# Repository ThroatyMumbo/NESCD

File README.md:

# NESCD-001

An unofficial homemade CD add-on for the NES, just because!

This repo contains the schematics, PCB, 3D printable STLs for the shell, sticker labels, and the firmware.

## How it works

It's basically an RP2350B hooked up to both an Everdrive N8 Pro and an IDE CD drive. It reads the game ROM off the CD, uploads it to the Everdrive over USB
and asks the menu to install it, then watches a mailbox byte in the cart's CHR RAM for the game to ask for music. The RP2350B is the coordinator in the
middle that bridges the NES/Everdrive and the CD drive.

Project video: https://www.youtube.com/watch?v=6D8RWVwW4ZI

## Hardware
- The main PCB (see [pcb/](pcb/))
- A standard 40-pin IDE CD drive
- Everdrive N8 Pro

## Build

```
cd firmware && ./flash.sh
```

## Making a disc

The demo game needs [cc65](https://cc65.github.io/) (`ca65`/`ld65`), plus
`python3` with `numpy`, `ffmpeg` for the audio, and `xorriso` to burn.

```
cd game && make         # demo.nes, four music tracks, and build/demo.img
cd game && make burn    # burn build/demo.img and read it back to check
```

To put your own game on a disc, pass [`mkgamedisc.py`](firmware/tools/mkgamedisc.py)
an iNES ROM and one track per music byte:

```
python3 firmware/tools/mktrack.py theme.wav -o theme.rom --loop-start 4.2
python3 firmware/tools/mkgamedisc.py -o mygame.img --title "MY GAME" --nes mygame.nes --track 1=theme.rom --verify
firmware/burn.sh mygame.img
```

## Using it

If everything goes right, you should be able to just put a burned disc into the CD drive while the NES is on and sitting on the Everdrive menu.
It'll auto-boot the game once it's read and uploaded to the Everdrive.

### Playing an audio CD

Arguably the most practical use for this thing: A CD player!

Insert the CD while on the Everdrive menu and it should automatically launch the player.

## FAQ

### What?
Great question! I came up with the idea for this project while reading about the canceled SNES CD-ROM add-on. I was originally going to make my own
version of that add-on, but decided it'd be funnier and weirder if I took it a step further and made one for NES.

### Why?
Because it's fun.

### Who?
It's me! Your old pal - Throaty Mumbo!

### Where are the FMVs you showed in the video?
I chose not to include any FMV-related code here because to get that working I had to semi-reverse engineer
Something Nerdy's [Bad Apple!! Ultimate NES Demake](https://somethingnerdy.com/downloads/), which is currently closed source.
The team has mentioned they're planning to formally open source their MXM mapper (which this demo presumably uses, actually not sure)
once their game *Former Dawn* is released. I didn't feel good about publishing reverse engineered code from an indie development team
for my stupid meme project, especially when they have plans to release it themselves.

### Why not stream audio from the Everdrive?
I originally wanted to do this, but was hitting a ceiling on the Everdrive USB bandwidth. I'd likely have to add some form of aggressive compression
to make room. It's also a nice touch to use the expansion port instead.

The USB cable poking out on the front is by far the biggest blemish on the design of this contraption, so I did look at moving everything to the
expansion port. Unfortunately the bandwidth there is even more limited than the USB route.

Plus, the expansion port audio allows more flexibility with mixing and volume control - hence the volume knob on the front.

### How is this thing powered?
A single molex cable from a wall adapter ([this one](https://www.amazon.com/Coolerguys-100-240v-Molex-Power-Adapter/dp/B000MGG6SC) in particular).
The 5V/12V rails are split between the CD drive and the board + the NES output. I took the end of a spare NES power cable and hooked it up to
a buck converter that converts the 12V input to ~9.5V so you can power the NES as well (the plug pokes out of the top of the box). That way
you only need one wall outlet to get the entire thing running. You can also power the NES separately from its regular adapter - the plug
coming out of the NESCD is optional.

### Couldn't you power everything off VRAW?
This was my initial plan, but it seemed tight considering the stock NES adapter (1.3A) has to power the NES, Everdrive, RP2350, DAC, and the CD drive.
The power adapter for that Fideco drive sled I tested with initially outputs at 2A, so I figured a dedicated 2A molex adapter (which supposedly outputs 2A on
5V and 12V each, at least according to the label) would be the minimum. But honestly I didn't actually test running the CD drive and everything else off
VRAW at the same time, so this was more of a cautious choice than based off of objective measurement. If it works it'd be a nice improvement for
an eventual v2 design.

### How do you get back to the Everdrive menu once you've inserted a disc?
This is still something I'm trying to figure out. AFAIK there's no way to trigger a soft reset on the NES. However one guaranteed solution is to
hook up the NES power output rail to a relay switch. That way if the board ever needs the NES to reset, it can just turn it on and off from the
source. Not super elegant but it should work.

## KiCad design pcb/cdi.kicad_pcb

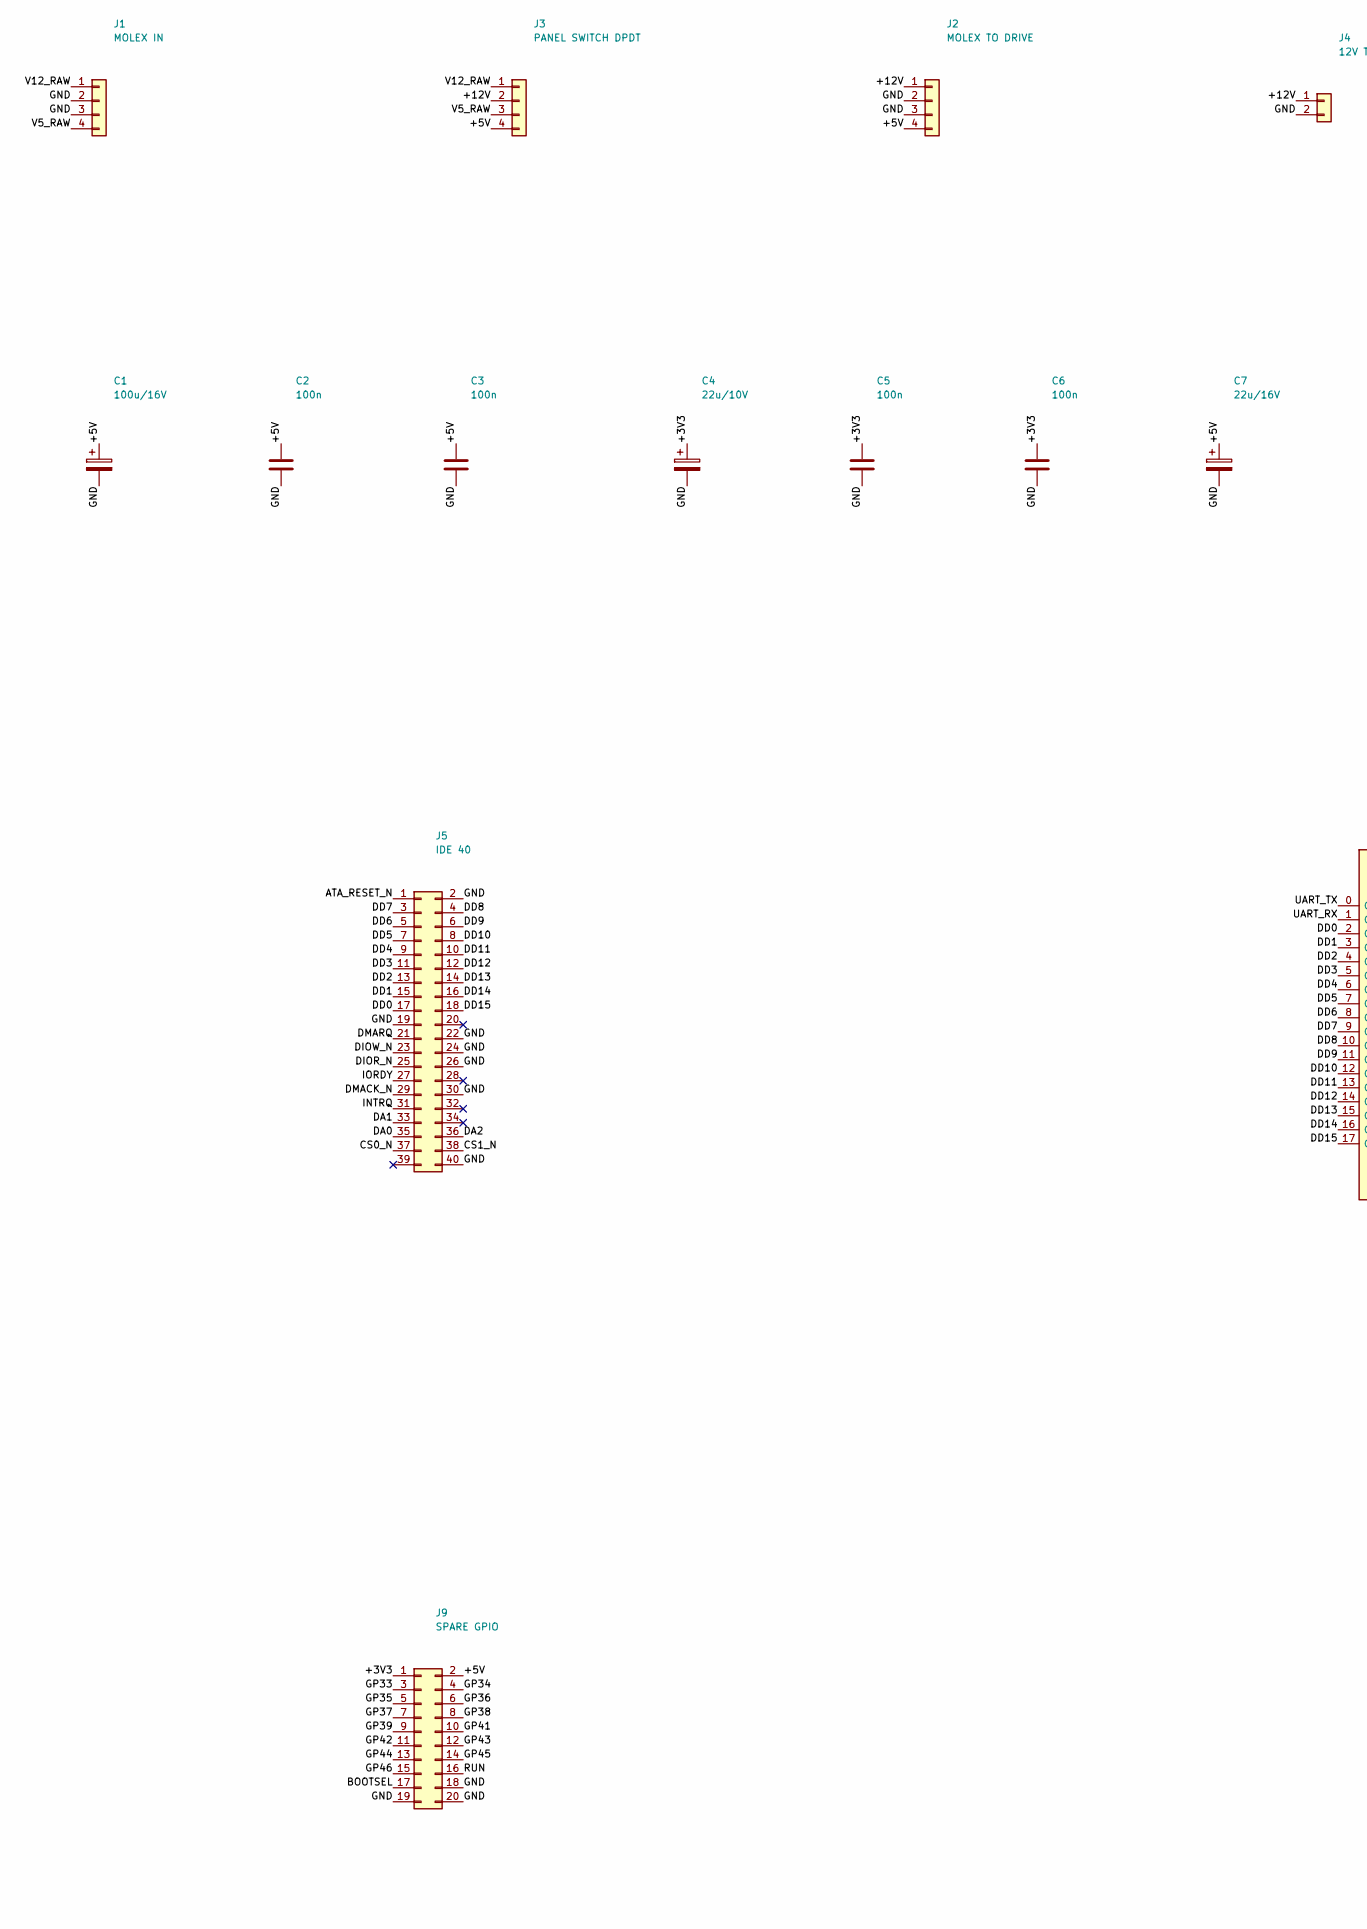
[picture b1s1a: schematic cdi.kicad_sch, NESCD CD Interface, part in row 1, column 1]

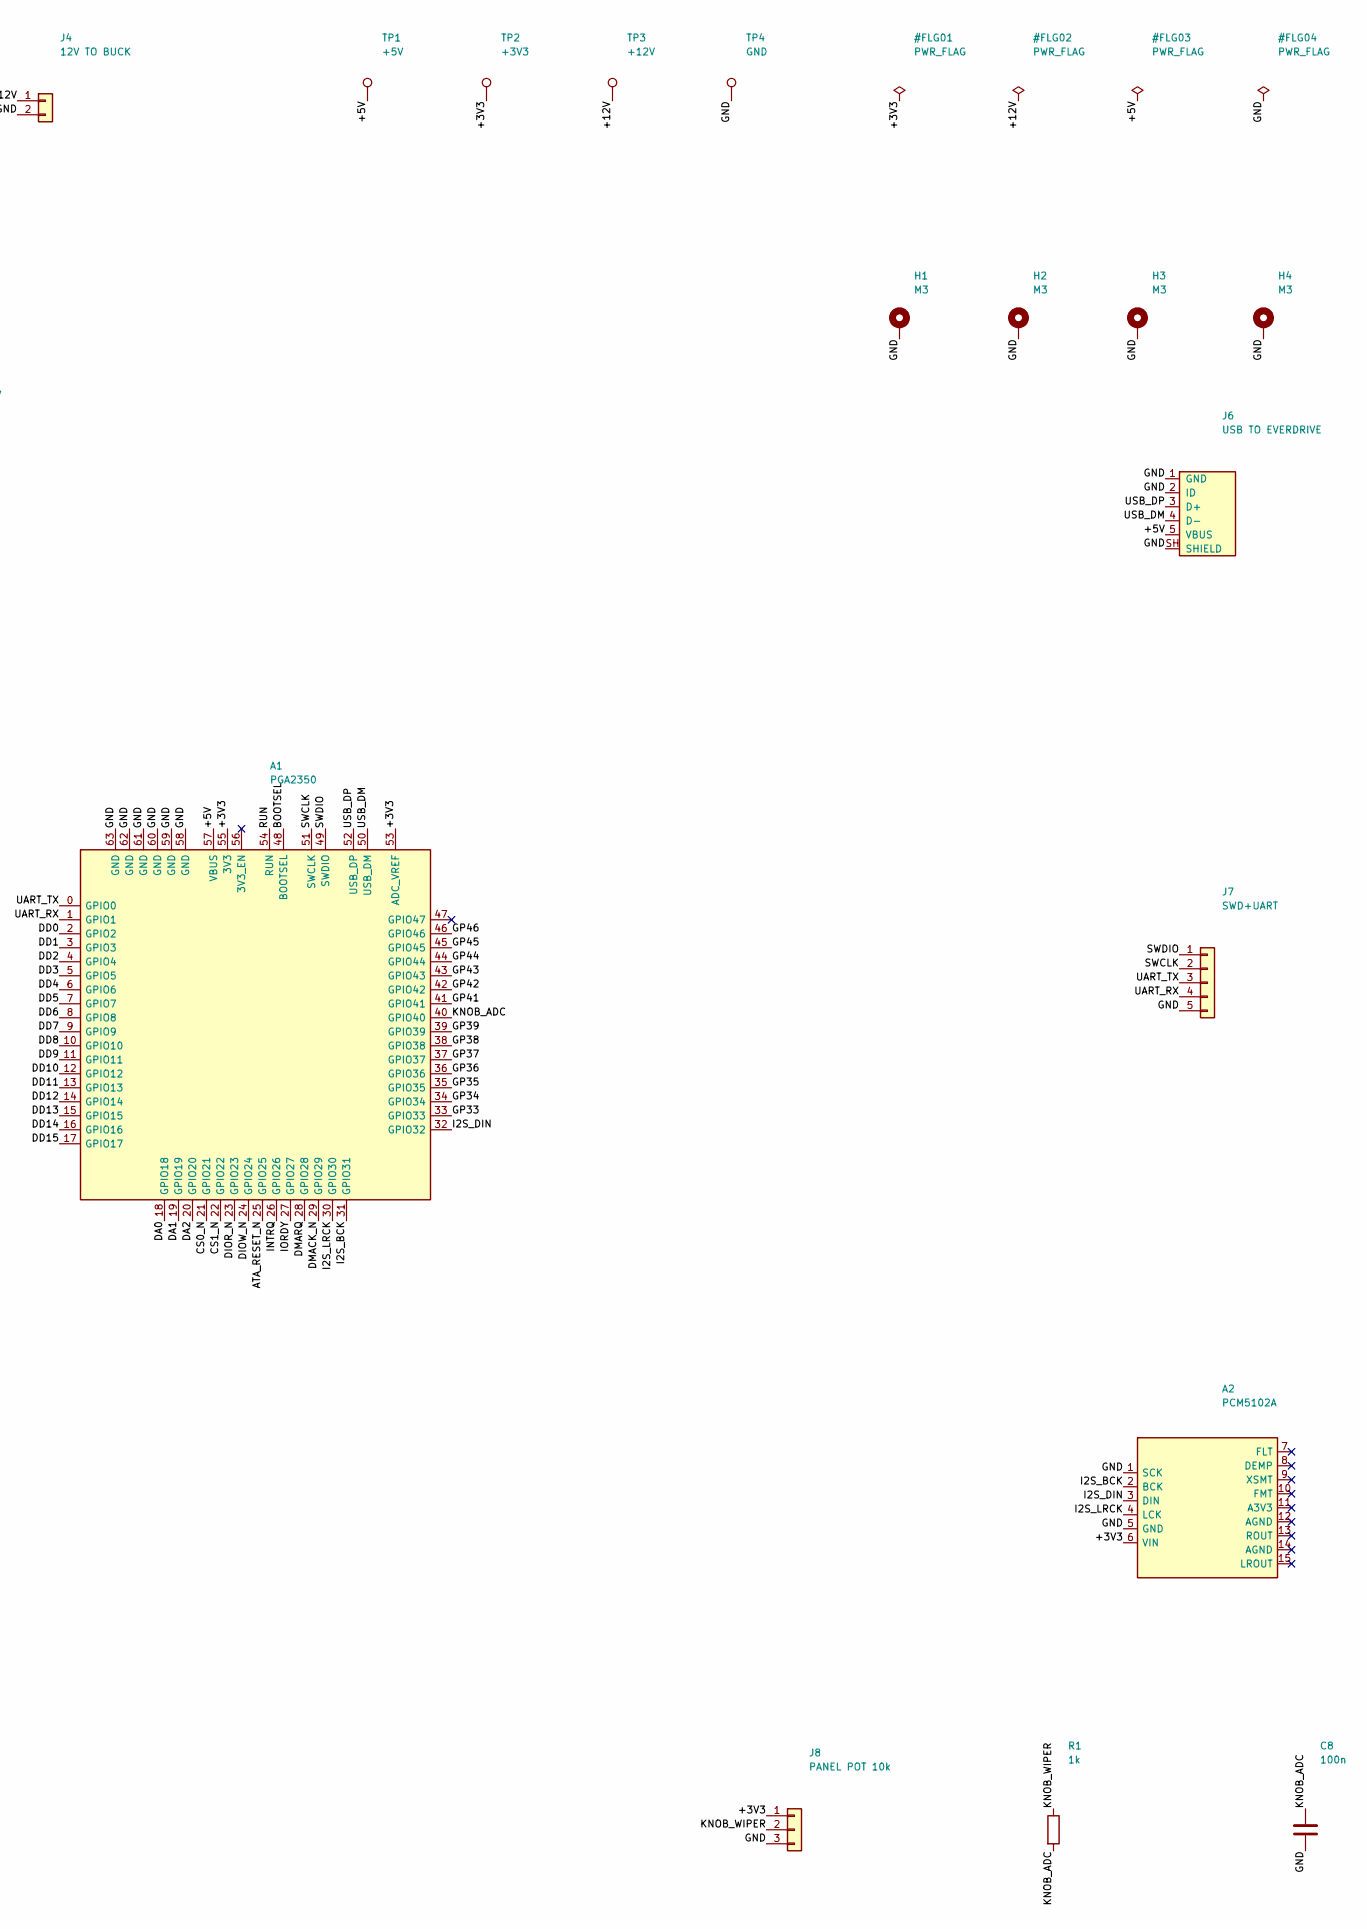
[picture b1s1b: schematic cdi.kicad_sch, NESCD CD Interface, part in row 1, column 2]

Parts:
A1: PGA2350; Pimoroni_PGA2350
A2: PCM5102A; PCM5102A_Board
C1: 100u/16V; CP_Radial_D6.3mm_P2.50mm
C2, C3, C5, C6, C8: 100n; C_Disc_D5.0mm_W2.5mm_P5.00mm
C4: 22u/10V; CP_Radial_D5.0mm_P2.50mm
C7: 22u/16V; CP_Radial_D5.0mm_P2.50mm
H1, H2, H3, H4: M3; MountingHole_3.2mm_M3_DIN965_Pad
J1: MOLEX IN; TE_MATE-N-LOK_350211-1_1x04_P5.08mm_Vertical
J2: MOLEX TO DRIVE; TE_MATE-N-LOK_350211-1_1x04_P5.08mm_Vertical
J3: PANEL SWITCH DPDT; TerminalBlock_Phoenix_MKDS-1,5-4-5.08_1x04_P5.08mm_Horizont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
J4: 12V TO BUCK; TerminalBlock_Phoenix_MKDS-1,5-2-5.08_1x02_P5.08mm_Horizont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
J5: IDE 40; IDC-Header_2x20_P2.54mm_Vertical
J6: USB TO EVERDRIVE; USB_Micro_DIP_1x05_P2.54mm
J7: SWD+UART; PinHeader_1x05_P2.54mm_Vertical
J8: PANEL POT 10k; PinHeader_1x03_P2.54mm_Vertical
J9: SPARE GPIO; PinHeader_2x10_P2.54mm_Vertical
R1: 1k; R_Axial_DIN0207_L6.3mm_D2.5mm_P7.62mm_Horizontal
TP1: +5V; TestPoint_THTPad_D1.5mm_Drill0.7mm
TP2: +3V3; TestPoint_THTPad_D1.5mm_Drill0.7mm
TP3: +12V; TestPoint_THTPad_D1.5mm_Drill0.7mm
TP4: GND; TestPoint_THTPad_D1.5mm_Drill0.7mm

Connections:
/+3V3: A1.53 (ADC_VREF), A1.55 (3V3), A2.6 (VIN), C4.1, C5.1, C6.1, J8.1, J9.1, TP2.1 (1_1)
/+5V: A1.57 (VBUS), C1.1, C2.1, C3.1, C7.1, J2.4, J3.4, J6.5 (VBUS), J9.2, TP1.1 (1_1)
/+12V: J2.1, J3.2, J4.1, TP3.1 (1_1)
/ATA_RESET_N: A1.25 (GPIO25), J5.1
/BOOTSEL: A1.48 (BOOTSEL), J9.17
/CS0_N: A1.21 (GPIO21), J5.37
/CS1_N: A1.22 (GPIO22), J5.38
/DA0: A1.18 (GPIO18), J5.35
/DA1: A1.19 (GPIO19), J5.33
/DA2: A1.20 (GPIO20), J5.36
/DD0: A1.2 (GPIO2), J5.17
/DD1: A1.3 (GPIO3), J5.15
/DD2: A1.4 (GPIO4), J5.13
/DD3: A1.5 (GPIO5), J5.11
/DD4: A1.6 (GPIO6), J5.9
/DD5: A1.7 (GPIO7), J5.7
/DD6: A1.8 (GPIO8), J5.5
/DD7: A1.9 (GPIO9), J5.3
/DD8: A1.10 (GPIO10), J5.4
/DD9: A1.11 (GPIO11), J5.6
/DD10: A1.12 (GPIO12), J5.8
/DD11: A1.13 (GPIO13), J5.10
/DD12: A1.14 (GPIO14), J5.12
/DD13: A1.15 (GPIO15), J5.14
/DD14: A1.16 (GPIO16), J5.16
/DD15: A1.17 (GPIO17), J5.18
/DIOR_N: A1.23 (GPIO23), J5.25
/DIOW_N: A1.24 (GPIO24), J5.23
/DMACK_N: A1.29 (GPIO29), J5.29
/DMARQ: A1.28 (GPIO28), J5.21
/GND: A1.58 (GND), A1.59 (GND), A1.60 (GND), A1.61 (GND), A1.62 (GND), A1.63 (GND), A2.1 (SCK), A2.5 (GND), C1.2, C2.2, C3.2, C4.2, C5.2, C6.2, C7.2, C8.2, H1.1 (1_1), H2.1 (1_1), H3.1 (1_1), H4.1 (1_1), J1.2, J1.3, J2.2, J2.3, J4.2, J5.2, J5.19, J5.22, J5.24, J5.26, J5.30, J5.40, J6.1 (GND), J6.2 (ID), J6.SH (SHIELD), J7.5, J8.3, J9.18, J9.19, J9.20, TP4.1 (1_1)
/GP33: A1.33 (GPIO33), J9.3
/GP34: A1.34 (GPIO34), J9.4
/GP35: A1.35 (GPIO35), J9.5
/GP36: A1.36 (GPIO36), J9.6
/GP37: A1.37 (GPIO37), J9.7
/GP38: A1.38 (GPIO38), J9.8
/GP39: A1.39 (GPIO39), J9.9
/GP41: A1.41 (GPIO41), J9.10
/GP42: A1.42 (GPIO42), J9.11
/GP43: A1.43 (GPIO43), J9.12
/GP44: A1.44 (GPIO44), J9.13
/GP45: A1.45 (GPIO45), J9.14
/GP46: A1.46 (GPIO46), J9.15
/I2S_BCK: A1.31 (GPIO31), A2.2 (BCK)
/I2S_DIN: A1.32 (GPIO32), A2.3 (DIN)
/I2S_LRCK: A1.30 (GPIO30), A2.4 (LCK)
/INTRQ: A1.26 (GPIO26), J5.31
/IORDY: A1.27 (GPIO27), J5.27
/KNOB_ADC: A1.40 (GPIO40), C8.1, R1.2
/KNOB_WIPER: J8.2, R1.1
/RUN: A1.54 (RUN), J9.16
/SWCLK: A1.51 (SWCLK), J7.2
/SWDIO: A1.49 (SWDIO), J7.1
/UART_RX: A1.1 (GPIO1), J7.4
/UART_TX: A1.0 (GPIO0), J7.3
/USB_DM: A1.50 (USB_DM), J6.4 (D-)
/USB_DP: A1.52 (USB_DP), J6.3 (D+)
/V5_RAW: J1.4, J3.3
/V12_RAW: J1.1, J3.1

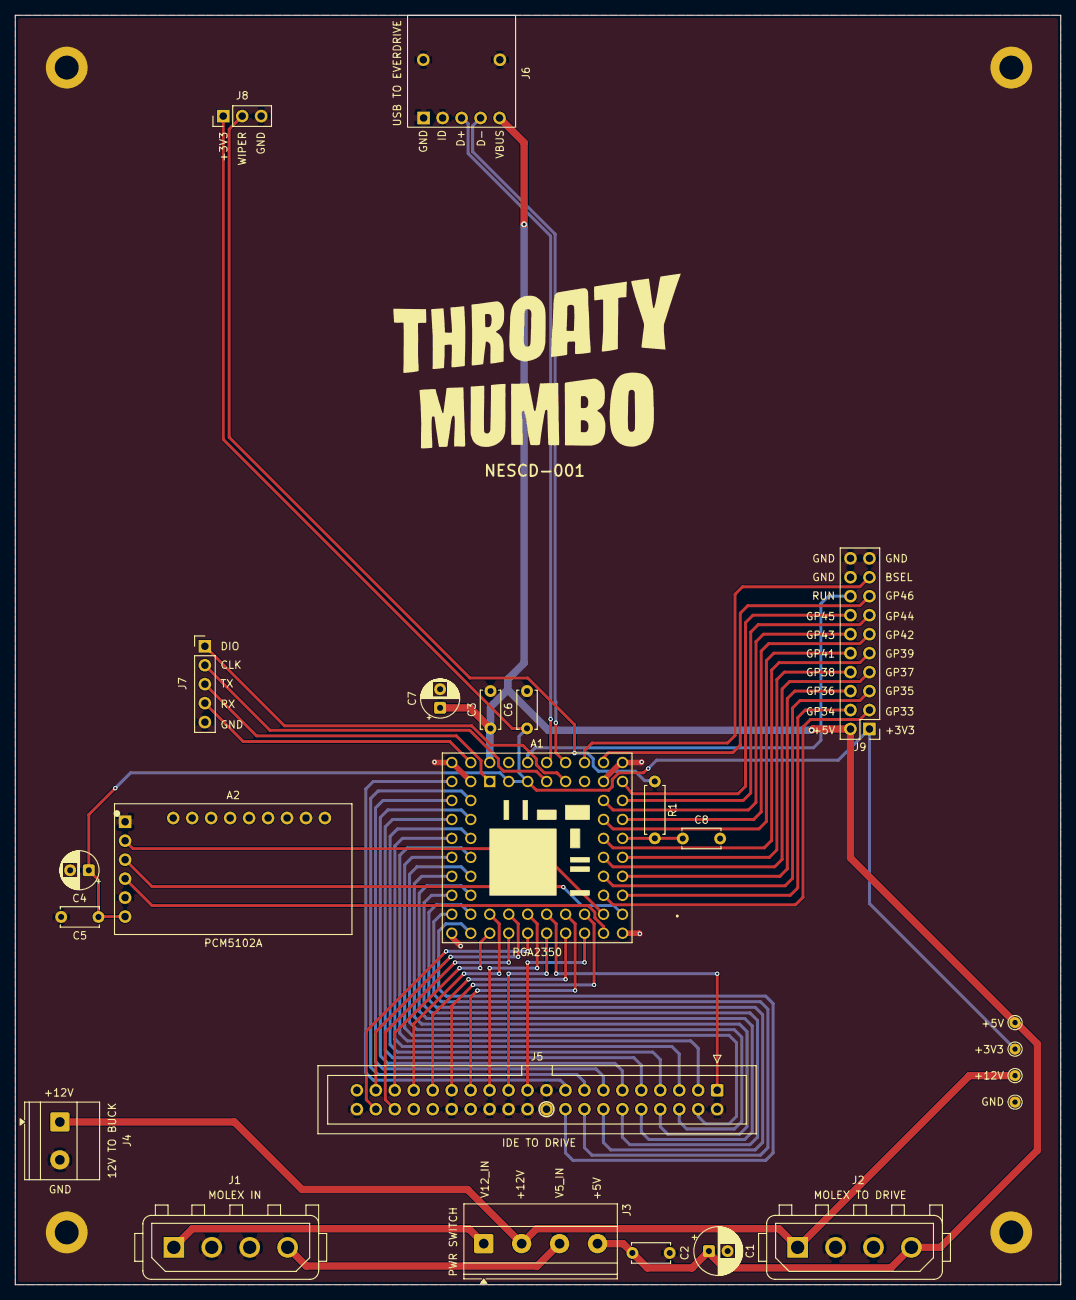
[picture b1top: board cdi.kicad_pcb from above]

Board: 2 copper layers, 140.0 x 170.0 mm, 28 parts (0 on the bottom side), 60 nets.

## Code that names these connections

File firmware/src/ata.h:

// ata.h - Parallel ATA taskfile host for the RP2350B (PGA2350).
//
// Role: HOST. This MCU is the IDE controller and drives any ATAPI CD-ROM
// (developed against a Pacific Digital MACH 52). The PACKET layer is atapi.c.
//
// The RP2350 is 5V tolerant, so the 40-pin ATA bus (5V TTL) connects DIRECTLY
// to GPIO - no level shifters, no transceivers.
//
// 40-pin ATA cable. Pin 20 is the key (no contact); tie every ground:
//   GND     pins 2,19,22,24,26,30,40
//   unused  pin 28 CSEL, 32 IOCS16#, 34 PDIAG#, 39 DASP#
//
// Jumper the drive to MASTER: it is the only device on the bus.

#ifndef ATA_H
#define ATA_H

#include <stdint.h>
#include <stdbool.h>
#include <stddef.h>
#include "pico/stdlib.h"

// ---- GPIO assignment (RP2350B / PGA2350) --------------------------------
// Reserved on this board: GP0/GP1 = UART0 console (debugprobe), GP47 = PSRAM CS.
// The bus is one contiguous block, GP2..GP29: inside a PIO GPIOBASE=0 window and
// below GP31, so gpio_get_all() and gpio_put_masked() still move the whole bus
// in one instruction.
#define PIN_DD0    2u          // DD0..DD15 = GPIO2..GPIO17 (bidirectional)
#define DD_MASK    (0xFFFFu << PIN_DD0)
#define PIN_DA0    18u         // out: register select bit 0   (ATA pin 35)
#define PIN_DA1    19u         // out: register select bit 1   (ATA pin 33)
#define PIN_DA2    20u         // out: register select bit 2   (ATA pin 36)
#define PIN_CS0    21u         // out: /CS0 command block      (ATA pin 37)
#define PIN_CS1    22u         // out: /CS1 control block      (ATA pin 38)
#define PIN_DIOR   23u         // out: /DIOR read strobe       (ATA pin 25)
#define PIN_DIOW   24u         // out: /DIOW write strobe      (ATA pin 23)
#define PIN_RESET  25u         // out: /RESET                  (ATA pin 1)
#define PIN_INTRQ  26u         // in : INTRQ                   (ATA pin 31)
#define PIN_IORDY  27u         // in : IORDY                   (ATA pin 27)
#define PIN_DMARQ  28u         // in : DMARQ                   (ATA pin 21)
#define PIN_DMACK  29u         // out: /DMACK                  (ATA pin 29)

// DA0..2 + both chip selects move together in one masked store.
#define ATA_ADDR_MASK (0x1Fu << PIN_DA0)

// DD0..DD15 interleave across the connector's two rows. Verify each line while
// wiring: ATA 17,15,13,11,9,7,5,3 = DD0..DD7, ATA 4,6,8,10,12,14,16,18 = DD8..DD15.

// ---- register blocks ----------------------------------------------------
#define ATA_CS_CMD 0u          // assert /CS0: command block
#define ATA_CS_CTL 1u          // assert /CS1: control block

// Command block (ATA_CS_CMD), selected by DA2:0.
#define ATA_REG_DATA      0u   // 16-bit
#define ATA_REG_ERROR     1u   // read
#define ATA_REG_FEATURES  1u   // write
#define ATA_REG_INTREASON 2u   // read  (ATAPI)
#define ATA_REG_SECCOUNT  2u   // write
#define ATA_REG_LBA_LOW   3u
#define ATA_REG_BCOUNT_LO 4u   // byte count low  (ATAPI)
#define ATA_REG_BCOUNT_HI 5u   // byte count high (ATAPI)
#define ATA_REG_DEVICE    6u   // DEV = bit 4
#define ATA_REG_STATUS    7u   // read
#define ATA_REG_COMMAND   7u   // write

// Control block (ATA_CS_CTL), DA=6.
#define ATA_REG_ALTSTATUS 6u   // read  (does not clear INTRQ)
#define ATA_REG_DEVCTL    6u   // write

// ---- status / device control bits ---------------------------------------
#define ATA_ST_BSY   0x80u
#define ATA_ST_DRDY  0x40u
#define ATA_ST_DF    0x20u
#define ATA_ST_DSC   0x10u
#define ATA_ST_DRQ   0x08u
#define ATA_ST_ERR   0x01u

#define ATA_DEVCTL_SRST 0x04u
#define ATA_DEVCTL_NIEN 0x02u

// ---- commands -----------------------------------------------------------
#define ATA_CMD_DEVICE_RESET    0x08u
#define ATA_CMD_PACKET          0xA0u
#define ATA_CMD_IDENTIFY_PACKET 0xA1u
#define ATA_CMD_SET_FEATURES    0xEFu
#define ATA_CMD_STANDBY_NOW     0xE0u
#define ATA_CMD_CHECK_POWER     0xE5u
#define ATA_FEAT_XFER_MODE      0x03u   // SECCOUNT = 0x00|mode for PIO flow

// ---- bus timing ---------------------------------------------------------
// Two PIO state machines own DD0..DD15 plus one strobe each; the CPU keeps
// DA0..2, CS0#, CS1#, RESET# and DMACK#. Timing is an ATA PIO mode rather
// than one uniform phase, so t1 setup, t2 pulse width and the recovery to t0
// are separate. Modes 3 and 4 are defined around IORDY flow control, which
// this driver does not implement, so only 0..2 are accepted.
#define ATA_PIO_MODE_MAX 2u

// Select a mode. Returns the achieved read cycle in ns, which is >= the mode
// minimum: the solver lengthens t0 rather than shortening any phase.
uint32_t ata_set_pio_mode(uint mode);

// Tell the drive which PIO mode it is about to be clocked at, before the host
// retimes. A rejection is survivable: mode 0 is the power-on default.
bool     ata_set_xfer_mode(uint mode);
uint     ata_get_pio_mode(void);
uint32_t ata_get_cycle_ns(void);
void     ata_timing_report(void);

// Bus occupancy, for the b benchmark's bus/wall split. Reset by the caller.
extern uint64_t ata_stat_words;
extern uint64_t ata_stat_bus_us;

// Called from inside ata_wait_not_bsy()/ata_wait_drq() while they spin, so a
// long ATA command does not starve whatever else the CPU owes time to.
// main() points this at usb_link_pump().
extern void (*ata_wait_hook)(void);

// Bring the pins up under SIO at their idle levels, then hand the data bus
// and both strobes to PIO and select Mode 0. False means no free state
// machines or program space, and the bus is left inert.
bool     ata_bus_init(void);

// SIO idle levels only. ata_bus_init() calls it first; diag.c calls it when
// putting the bus back after driving pins itself.
void     ata_gpio_init(void);
void     ata_hard_reset(void);
bool     ata_soft_reset(uint32_t timeout_ms);

uint8_t  ata_reg_read8(uint cs, uint da);
void     ata_reg_write8(uint cs, uint da, uint8_t v);
uint8_t  ata_status(void);
uint8_t  ata_altstatus(void);

// Burst transfers hold the address static and strobe only /DIOR or /DIOW.
// Any word count is accepted; an odd one costs no extra bus cycle.
void     ata_read_data_burst(uint16_t *dst, size_t words);
void     ata_write_data_burst(const uint16_t *src, size_t words);

// Strobe /DIOR the given number of times and throw the data away. The drive
// announces a burst size the host may not have room for, and draining it a
// word at a time through ata_read_data_burst() costs several times as much.
void     ata_skip_data(size_t words);

// DMA-backed read that returns immediately, so the caller can do something
// useful while the bus runs. begin() returns false when the fast path does
// not apply - an unaligned destination, an odd count, or a read already in
// flight - and the caller should fall back to ata_read_data_burst().
bool     ata_read_begin(uint16_t *dst, size_t words);
bool     ata_read_poll(void);
void     ata_read_end(void);

// Hand every ATA pin back to SIO at its idle level, and take it back again.
// diag.c drives pins directly and needs the bus for the duration.
void     ata_bus_release(void);
void     ata_bus_take(void);

// Force both strobes high and restart both machines. A disabled state machine
// holds whatever the PIO output register last latched, so lifting a stuck
// strobe means writing that register, not just stopping the machine.
void     ata_bus_recover(void);

bool     ata_wait_not_bsy(uint32_t timeout_ms);
bool     ata_wait_drq(uint32_t timeout_ms);
void     ata_select_device(uint dev);

// Wait for the drive to post its ATAPI signature after a reset. Status is
// useless here: a packet device idles at 0x00, and a floating bus reads 0x7F
// because DD7 alone carries no pull-up.
bool     ata_wait_signature(uint32_t timeout_ms);

// Post-reset signature: mid 0x14 / high 0xEB marks an ATAPI packet device.
void     ata_read_signature(uint8_t *mid, uint8_t *high);

// IDENTIFY PACKET DEVICE (0xA1) into 256 words. A packet device aborts the
// plain IDENTIFY DEVICE (0xEC), so this is the one that works on a CD-ROM.
bool     ata_identify_packet(uint16_t *id256);
int      ata_nondata(uint8_t cmd);

// Extract a byte-swapped ASCII field from an IDENTIFY buffer (model = words
// 27..46, firmware = 23..26, serial = 10..19), trimming trailing spaces.
void     ata_id_string(const uint16_t *id, int first, int nwords,
                       char *out, int outsz);

#endif
